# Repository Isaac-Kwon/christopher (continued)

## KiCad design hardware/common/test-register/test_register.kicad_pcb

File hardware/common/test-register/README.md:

# 테스트 레지스터 보드 (Phase 3.0, 산출물 4)

작성일: 2026-11-15 · 상태: **회로도(KiCad 10) + 스위치 수준 시뮬레이션 통과 + 부품 배치(미배선) PCB, 결정 0003 8.1절(R1–R8) 반영(3.3절), 배선·실기 시험은 아직** · 관련: `docs/decisions/0001-test-register-timing.md`, `docs/decisions/0003-interfaces.md`, `hardware/common/design-brief.md` 4.2·4.5·12절(결정 10), `hardware/common/unit-tester/README.md` 3.4절(커넥터 규약), `report/figures/hw-register-circuit.tex`

**표기.** **(추정)** 은 계산·경험에 따른 값으로 실측 전이고, **(미확인)** 은 부품 번호·사양을 데이터시트로 확인하지 못한 것이다. 시뮬레이션이 쓴 릴레이 시간은 결정 0001의 표 값이다.

## 1. 한 줄 요약

감지 릴레이 K1–K26이 `STROBE` 창 안에서 자기 유지로 잡히고(선마다 역류 차단 다이오드), 통과 릴레이 P·정지 릴레이 S·판정 접점 j가 `STROBE`가 끝난 뒤 `JUDGE` 구간에 "26선이 전부 통전되지는 않았는가"를 판정하며, `CLEAR` 구간에 유지 버스 H를 끊어 K와 P를 놓는다. 정지하면 S가 자기 유지하고 H를 우회시켜 K 26개의 상태(램프 표시)를 붙들며, `RUN`을 내리고 시험 전압을 끊는다. 신호 릴레이(G6S-2, DPDT) 34개, 표시 구동 MOSFET 28개.

## 2. 파일

| 파일 | 내용 |
|---|---|
| `gen_register.py` | KiCad 10 회로도 생성(표준 라이브러리 기호 복사). `test_register.kicad_pro/.kicad_sch`(루트: 제어부·커넥터·전원) + `sense_lanes.kicad_sch`(K 26 레인) |
| `verify_register.py` | 넷리스트 내보내기(kicad-cli) → 스위치 수준·사건 구동 시뮬레이션 + 변형 넷리스트 음성 시험 |
| `gen_pcb.py` | 넷리스트 + 푸트프린트 라이브러리 → `test_register.kicad_pcb`(배치·외곽·넷, 미배선). `--check`: 배치된 기판의 패드 넷 = 회로도, DRC, 래츠넷, 재생성 동일, 음성 시험 |
| `test_register.kicad_*` | 생성물(손으로 고치지 않는다) |

재생성: `python gen_register.py && python gen_pcb.py`, 검증: `python verify_register.py [--quick]`, `python gen_pcb.py --check`. KiCad가 기본 위치에 없으면 환경 변수 `KICAD_SHARE`(기호·푸트프린트), `KICAD_CLI`를 준다.

## 3. 회로 (결정 0001 (c) 채택안과의 대응)

릴레이 접점은 소문자(k, p, s, j, r), 코일은 대문자. 모든 릴레이는 G6S-2 24 V (코일 1 = +, 12 = −; 극 1 = COM 4/NC 3/NO 5, 극 2 = COM 9/NC 10/NO 8).

| 요소 | 참조 | 회로 |
|---|---|---|
| 감지 릴레이 K_i | K1–K26 | 코일은 노드 N_i에 연결. N_i ← 차단 다이오드 D_i ← 선 L_i(J1). 극 1 = 유지 접점(H → N_i), 극 2 = 사슬 접점. 코일 역기전력 다이오드 DF_i |
| 유지 버스 H | | HSUP → `r`(CLEAR 릴레이 K29의 b접점, 두 극 병렬) → H. 정지 중에는 S1의 극 1이 HSUP → H를 우회 |
| 사슬 | | H → k_A → k_B → … → k_Z → PN(P 코일). **26선이 전부 유지 중일 때만 PN이 선다** |
| 통과 릴레이 P | K30 | 코일 PN. 극 1 = 자기 유지(H → p → 다이오드 D33 → PN), 극 2 b접점 = 판정 경로 j → p → S 코일 |
| 판정 접점 j | K28 | `JUDGE` 입력으로 구동되는 릴레이의 a접점(두 극 병렬): +24 V → JNODE |
| 정지 릴레이 S | K31–K33 | 코일 3개를 SN에 병렬(극 6개 필요). S1: H 우회, 자기 유지(HSUP → s → SN). S2: P 구동(HSUP → s → PN, 재출발 잠금), 시험 전압 차단(b접점). S3: `RUN` 차단(b접점), `STOP_LATCH`를 뱅크로 |
| `STROBE` 릴레이 | K27 | `STROBE` 입력(J2 1번 → 직렬 다이오드 D34 → 코일)으로 구동. a접점(두 극 병렬)이 +24 V → S2 b접점 → TEST(J5)를 연결 |
| `CLEAR` 릴레이 r | K29 | `CLEAR` 입력(J2 35번 → D36 → 코일)으로 구동. b접점이 CLEAR 구간에 H의 공급을 끊는다. `JUDGE`(K28)는 J2 34번 → D35 → 코일 |
| 해제 릴레이 | K34 | 앞면 해제 누름 버튼(상시 열림)이 구동. b접점 두 개: `RUN` 경로, HSUP(H와 S 자기 유지의 공급). 누르는 동안 S가 풀리고 K·P가 모두 놓이며 `RUN`이 내려간다 |
| 램프 구동 | Q1–Q26, Q27, Q28 | N_i → 분압(RA 33 k/RB 22 k, Vgs < 12 V) → AO3400A. 드레인 = LAMP_i(J3), 소스 = LAMPGND. Q27이 SN으로 LAMPGND를 0 V에 잇는다(정지 중에만). Q28은 정지 램프(LAMP_STOP) |
| 보드 위 표시 | DL1–DL26, DL27 | N_i → 3.3 k → LED → LAMPGND(정지 중에만 켜짐). DL27 = 정지(S 동작). DI1–DI4 = `STROBE`/`JUDGE`/`CLEAR`/`STOPPED` 입력 표시 |

### 3.1 시간표와 회로의 동작 (60 rpm, 한 위치 38.5 ms)

시뮬레이션은 뱅크가 각 신호를 릴레이 동작 시간만큼 앞서 보내 **접점**의 창이 결정 0001의 표와 같도록 한다(보정, G.1 측정 5).

| 구간 (ms) | 접점 | 일어나는 일 |
|---|---|---|
| 0 – 6 | TEST (K27) | 통전된 선의 D_i → N_i → K_i 코일. K_i 동작(최악 5 ms)하면 k(유지)가 N_i를 H에 이어 스스로 유지 |
| 6 – 12 | | 사슬이 닫혔으면(26선 전부) PN이 서고 P 동작(최악 5 ms, 최대 10 ms까지). p(유지)가 H로 P를 유지, p b접점이 열림 |
| 12 – 19 | j (K28) | P가 놓여 있으면 JNODE → p b접점 → SN 에 전압이 걸려 S 코일 3개 동작(최악 5 ms). S가 동작하면 자기 유지, H 우회, P 잠금, TEST 차단, `RUN` 차단, 램프 점등 |
| 21 – 33 | r (K29) | H 공급이 끊겨 K와 P가 놓임(최악 10 ms → 31 ms). 정지 중이면 S1이 H를 우회하므로 아무것도 놓이지 않는다 |
| 33 – 38.5 | | r이 다시 닫혀 H 복구, 다음 `STROBE` 대기 |

재출발: 해제 버튼(J6 핀 3)을 누르면 K34가 동작해 HSUP이 끊긴다. S의 자기 유지와 H가 함께 끊겨 S, K, P가 모두 놓이고 램프가 꺼지며 `RUN`은 K34가 놓일 때까지 낮다. **버튼은 약 50 ms 이상 누른다(K·P의 복귀 최악 10 ms + K34의 동작 시간)**. K34의 자체 복귀 시간이 접점 튐을 흡수한다.

### 3.2 결정 0001 회로도에서 고친 곳 (보고서 그림 `fig:hw-register`와 달라진 점)

시뮬레이션이 드러낸 것이다. 보고서 그림(`report/figures/hw-register-circuit.tex`)과 결정 0001 본문(3절, 6·7절)에 반영했다(2026-11-16).

1. **사슬의 공급은 +24 V가 아니라 H다.** 사슬을 +24 V에서 먹이면 K가 모두 붙은 위치에서 P의 코일이 CLEAR 중에도 사슬에서 전압을 받아, P의 복귀가 첫 K의 복귀 뒤에야 시작된다(K 3–10 ms + P 3–10 ms). 시뮬레이션에서 H가 복구되는 33 ms 시점에 P가 아직 동작 중이어서 P가 다음 주기까지 남았다(오래 남은 P는 거짓 통과, 곧 놓친 정지). H에서 먹이면 K와 P가 같은 순간(`r`이 열릴 때) 복귀를 시작하므로 결정 0001의 "최악 10 ms" 계산이 성립한다.
2. **P의 자기 유지 접점에 다이오드(D33).** 정지 잠금(S2의 p 구동)이나 사슬이 PN에 전압을 주면 p 접점을 거꾸로 H로 흘러, H가 끊겨야 할 때 끊기지 않는다.
3. **정지 잠금과 S의 자기 유지는 +24 V가 아니라 HSUP에서 받는다.** 그래야 해제 버튼 하나로 S, P, K가 함께 풀린다.
4. **해제 릴레이 K34(추가).** 결정 0001 4절 3항은 해제 버튼으로 S만 풀어도 P가 "다음 복귀 구간에서" K와 함께 풀린다고 했다. 그러나 정지 직후 뱅크가 `CLEAR` 없이 다음 `STROBE`로 넘어가면(정지 중 이미 `CLEAR`가 지나갔다), 정지 위치의 K 26개가 남은 채 다음 위치의 선이 덧붙고 P가 잠겨 있어 **다음 위치에서 정지를 놓친다.** 해제 때 보드가 직접 H를 끊어 K·P를 지우면 뱅크가 재출발 때 `CLEAR`를 한 번 더 내야 하는 요구가 사라진다. (뱅크가 재출발 때 `CLEAR` 한 번을 보장한다면 K34는 빼고 버튼을 S 자기 유지 경로의 b접점으로 쓸 수 있다.)
5. **감지 릴레이의 접점 수.** K 하나에 유지·사슬 두 극이면 충분하다(DPDT 1개). 램프는 접점이 아니라 N_i 전압을 읽는 MOSFET이 구동한다(표시 릴레이 26개의 전류가 H·유지 접점을 지나지 않게 하려는 것).

### 3.3 결정 0003 반영 (8.1절)

| # | 변경 | 상태 |
|---|---|---|
| R1 | 타이밍 입력 셋(J2 1·34·35번)에 직렬 다이오드(핀 → D34·D35·D36 → 코일). 다이오드 + 제너 30 V 클램프(D27–D29, DZ27–DZ29)는 코일 쪽 마디(`STROBE_C` 등)에 그대로, 표시 LED·저항(RI1–RI3)은 핀 쪽에 남겨 풀다운 역할. 시뮬레이션의 지연 가정은 그대로. 이유: 신호가 꺼질 때 코일의 + 쪽이 핀을 약 −31 V까지 끌어내리던 것을 막아 기어식의 광센서 출력과 고측 구동기가 견디게 한다(0003 2.2절) | 적용 |
| R2 | J2 36번 `STOP_LATCH`: "제안" 표기를 지우고 확정 | 적용(4절) |
| R3 | J2 22–23번(`ESTOP_A/B`)과 24–25번(`ILOCK_A/B`): 미연결 → **납땜 점퍼(기본 닫힘) SJ1·SJ2**로 각각 잇는다. 22·23번은 J6의 6·7번으로도 낸다(비상 정지 버튼의 b접점을 달면 SJ1을 끊는다) | 적용 |
| R4 | J6을 4극 → 8극: 5번 = Home 버튼 되돌림 → J2 4번(`HOME`, 풀다운 RR4 100 kΩ), 6·7번 = 비상 정지 버튼, 8번 예약. 레지스터는 `HOME`을 쓰지 않고 뱅크로 곧바로 보낸다 | 적용 |
| R5 | D-sub 세 개의 껍데기(풋프린트 패드 `SH`; 심볼에 핀이 없어 PCB 생성기가 붙임)와 도금 장착 구멍 H1–H4를 `CHASSIS`로, `CHASSIS`–0 V에 RCH1 1 MΩ ∥ CCH1 10 nF/100 V | 적용 |
| R6 | 전원 입력에 직렬 P채널 MOSFET QP1(SOT-223, 드레인 = J4 쪽, 게이트에 DZP1 12 V 제너 + RGP1 100 kΩ), F1·F2 앞 공용, TVS DV1은 그 뒤 | 적용 |
| R7 | 이 README: `STROBE`·`JUDGE`·`CLEAR`는 24 V 레벨로 확정(7절 2번), 뱅크의 요구는 0003 3.3절의 L1–L9, 시작 스위치는 유지형, 표시 코일은 60 mA 이하·다이오드만(7.5절), J2 26–27번은 미연결 유지 | 적용(7절, 4절) |
| R8 | 바뀌지 않는 것: J1의 27–29번 = 0 V, 암수(핀), J3·J4·J5의 핀 배치 | 확인 |

## 4. 커넥터와 핀 배치

D-sub 37은 시프터 보드(J1–J4)와 같은 `DC37_Pins`(보드 쪽 핀, 케이블 쪽 소켓)이며 핀 1–26 = 선 A–Z 규약은 단위 시험기와 같다. 뱅크 제어 커넥터는 시험기 J_C와 겹치는 핀이 같은 번호다.

**J1 — 테스트 레지스터 케이블 (메뉴 패널에서 26선)**

| 핀 | 신호 |
|---|---|
| 1–26 | L_A … L_Z (감지 릴레이 입력) |
| 27–29 | 0 V |
| 30–37 | 예약(미연결) |

**J2 — 뱅크 제어 (시험기 J_C 규약)**

| 핀 | 신호 | 방향 |
|---|---|---|
| 1 | `STROBE` (24 V 레벨, 높음 = 시험 구간) | 뱅크 → 보드 |
| 2 | `RUN` (24 V = 진행 허가, 정지하면 낮음) | 보드 → 뱅크 |
| 3 | `STOPPED` (표시 LED만) | 뱅크 → 보드 |
| 4 | `HOME` (24 V, 앞면 패널의 Home 버튼 되돌림 = J6 5번에서 곧바로. 풀다운 100 kΩ. 레지스터는 쓰지 않는다) | 보드 → 뱅크 |
| 22, 23 | `ESTOP_A`, `ESTOP_B`: 뱅크가 22번으로 내보내고 23번으로 받는다. 보드에서 SJ1(기본 닫힘)이 잇고 J6 6·7번으로도 나간다 | 고리 |
| 24, 25 | `ILOCK_A`, `ILOCK_B`: 같음, SJ2(기본 닫힘) | 고리 |
| 34 | `JUDGE` (24 V, 높음 = 판정 구간) | 뱅크 → 보드 |
| 35 | `CLEAR` (24 V, 높음 = 복귀 구간) | 뱅크 → 보드 |
| 36 | `STOP_LATCH` (**확정**: S 동작 = 24 V, 결정 0003 5.2절) | 보드 → 뱅크 |
| 28–33 | 0 V | |
| 5–21, 26–27, 37 | 미연결 (AT_HOME, END, POS, 뱅크 전원 26–27: 이 보드는 쓰지 않는다. 예약 핀은 어느 보드에서도 잇지 않는다) | |

타이밍 입력(1·34·35번)은 24 V 레벨이고 핀 쪽에 음전압을 내보내지 않는다(R1). 받는 쪽 규격: 18 V 이상에서 켜지고 2.4 V 이하에서 꺼진다, 핀당 15 mA 이하(코일 약 8 mA, 직렬 다이오드 0.7 V를 빼면 코일에 약 22.3 V = 정격의 93 %).

**J3 — 표시(램프 패널)**

| 핀 | 신호 |
|---|---|
| 1–26 | LAMP_A … LAMP_Z. 열린 드레인: **낮음 = 그 글자의 표시 릴레이(또는 램프)를 켠다**. 정지 중 K_i가 유지 중인(= 시험 순간에 통전된) 글자만 켜진다 |
| 27 | LAMP_STOP (낮음 = 정지 램프) |
| 28–30 | +24 V (F2 2 A 보호, 표시 릴레이 코일의 + 쪽) |
| 31–37 | 0 V |

표시 쪽: 클리어 케이스 범용 종속 릴레이(결정 10)의 코일을 +24 V와 LAMP_i 사이에 연결하고, 코일마다 역기전력 다이오드를 **표시 쪽**에 둔다. 켜진 램프를 "통전된 글자"로 볼지 "꺼진 글자(스테커 후보)"로 볼지는 표시 릴레이의 a접점/b접점 선택으로 정한다(design-brief 4.5·4.6절의 표현이 엇갈린다는 결정 0001 4절 지적에 대한 처리: 보드는 한 극성만 내고 표시 쪽이 고른다).

**J4** 24 V 입력 (1 = +24 V, 2 = 0 V, 스크루 단자; 역극성 P채널 MOSFET QP1 → F1·F2) · **J5** 시험 전압 선 (1 = TEST: `STROBE` 중 +24 V, 2 = 0 V; 메뉴 패널의 시험 선 플러그로) · **J6** 앞면 패널, 8극 (1 = +24 V 스위치 공통, 2 = 시작 스위치 되돌림(**유지형**: 켜짐/꺼짐이 남는 스위치. 순간 버튼과 자기 유지 릴레이를 따로 두지 않는다), 3 = 해제 누름 버튼 되돌림(상시 열림, 50 ms 이상), 4 = 0 V, 5 = Home 버튼 되돌림 → J2 4번, 6·7 = 비상 정지 버튼의 b접점 → J2 22·23번(버튼이 없으면 SJ1 닫힘), 8 예약). D-sub 껍데기·장착 구멍 = `CHASSIS`(0 V가 아님).

## 5. 릴레이 수와 전력

| 용도 | 수 | 부품 |
|---|---:|---|
| 감지 K | 26 | G6S-2 DC24 (DPDT 신호 릴레이, 투명 케이스 범용 아님: 결정 10) |
| 통과 P | 1 | 같음 |
| 정지 S | 3 | 같음, 코일 병렬 (접점 극 6개 필요) |
| `STROBE`·`JUDGE`·`CLEAR` 릴레이 | 3 | 같음 (코일 역기전력은 다이오드 + 제너 30 V 직렬: 복귀 1.5–4 ms) |
| 해제 | 1 | 같음 |
| **신호 릴레이 합계** | **34** | 표시용 종속 릴레이 26 + 정지 램프는 표시 쪽 부품(보드 밖) |

그 밖: 다이오드 1N4148W 62(차단 26, 코일 26, 클램프·유지 7, 타이밍 입력 직렬 3) + 제너 3(30 V) + 제너 1(12 V 게이트) + TVS 1, MOSFET AO3400A 28 + 직렬 P채널 1, 저항 91, LED 31, PTC 2, 전해 커패시터 2(100 µF/35 V) + 10 nF 1, 납땜 점퍼 2, D-sub 37 3, 스크루 단자 3(J6은 8극), 도금 장착 구멍 4. 넷리스트의 부품은 269개.

전류 **(추정)**: 코일 한 개 약 8 mA(24 V, 결정 0001). 최악(26 K 유지 + P + S + 타이밍·해제 릴레이)은 0.3 A 안팎이고 정지 중 보드 위 LED가 0.17 A를 더한다. 논리 쪽 F1은 1.1 A 유지형을 둔다. 표시 쪽 전류는 보드를 지나지 않고 J3의 +24 V → 표시 릴레이 → LAMP_i → Q_i/Q27 → 0 V로 흐른다. 26개가 모두 켜지고 코일이 약 60 mA라면 1.6 A이므로 F2는 2 A 유지형, Q27은 AO3400A(5.7 A)다. 표시 릴레이의 실제 코일 전류는 부품을 정하면 확인한다.

## 6. 검증

### 6.1 ERC와 넷리스트
`kicad-cli sch erc`: 위반 0(오류·경고 0). 넷리스트 269부품·295넷.

### 6.2 스위치 수준 시뮬레이션 (`verify_register.py`)
넷리스트의 핀 소속만으로 릴레이 접점·다이오드·MOSFET·퓨즈를 풀어 HIGH/LOW를 구하고(둘 다면 단락으로 보고), 릴레이는 코일이 동작(복귀) 시간 동안 끊김 없이 구동될 때만 바뀐다. 시간은 사건 구동(ms)이다. 릴레이 시간 **(결정 0001 표)**: K·P·S·해제 동작 2.5–5 ms(접점 안정 포함), 복귀 3–10 ms(다이오드); `STROBE`·`JUDGE`·`CLEAR` 릴레이 동작 2.5–4 ms, 복귀 1.5–4 ms. 시험대는 뱅크(신호)와 메뉴 배선망(통전된 선 집합 A를 `STROBE` 중에만 시험 선에 잇고, 그 밖에는 무관한 집합 B를 시험 선에 잇는다: 드럼이 움직이는 동안의 역류 경로 시험)을 흉내 낸다.

결과(전체 실행, `python verify_register.py`):

- **통과**(결정 0003 반영 후 같은 값): 438 위치 주기, 176회 정지, 26선 전부 통전 때 거짓 정지 0. 확인 항목: K가 통전된 선만 정확히 유지, P는 26선 전부일 때만 동작, S는 26선이 전부는 아닐 때만 동작·유지, 램프(J3 구동선과 보드 LED)는 **정지 중에만** 유지된 패턴을 보이고, `CLEAR`가 정지가 아닐 때 모든 릴레이를 놓으며, 정지 중에는 K·P·S·램프가 뒤이은 주기(뱅크가 `RUN`을 무시하고 계속 돌 때, 다른 패턴으로)에도 얼어 있고 시험 전압이 끊겨 있으며, 해제가 모두 지우고 `RUN`을 되돌린다.
- 사례: 26선 전부(연속 3위치) / 25선(글자별 26가지) / 1선(26가지) / 0선 / 무작위 부분집합 120(크기 0–26) / 정지·정지 중 주행·해제를 섞은 순서 12 / 모든 릴레이가 최악·최선 시간인 모서리 사례.
- **놓친 정지 시험**: 비정상 `STROBE` 창(2–8 ms)과 무작위 릴레이 시간 60회에서 **놓친 정지 0**, 거짓 정지 6(창이 K 동작보다 짧을 때: 안전한 쪽).
- **최악 릴레이 시간에서의 최소 여유(보드가 뱅크에 요구하는 값)**: `STROBE` 전기적 창 ≥ 5.0 ms(K 최악 동작), `JUDGE` 접점 폭 ≥ 5.0 ms(S 최악 동작; 이보다 짧으면 **정지를 놓친다**), `CLEAR` 접점 폭 ≥ 10.0 ms(K 최악 복귀; 이보다 짧으면 H가 복구될 때 K가 다시 붙어 **지워지지 않는다**). 결정 0001의 창 6 / 7 / 12 ms는 이를 만족한다.
- **음성 시험 18가지**(변형 넷리스트는 모두 실패해야 한다): 차단 다이오드 뒤집기(2), K 유지·사슬 접점 NO/NC 바꾸기(3), P의 자기 유지·판정 경로(2), S1의 자기 유지·H 우회, S2의 P 잠금·시험 차단, S3의 `RUN` 차단, `STROBE` 접점, `CLEAR` 릴레이, 해제 릴레이, `JUDGE`/`CLEAR` 입력 바꾸기, 램프 두 선 바꾸기, 시험 선 두 개 바꾸기. 모두 검출됨.

- **드럼 선 무전류 검사 (결정 0003 L9, 2026-11-16).** 정적: J1의 각 선 L_i 마디는 J1.i와 차단 다이오드 D_i 애노드뿐이고(D_i 캐소드 = K_i 코일 +), 시험 전압 선 J5.1은 K27의 NO 접점 두 개뿐이다. 동적: 모든 평가 시점(JUDGE·CLEAR·정지·해제 포함)에서 K27 접점이 열려 있으면 어떤 J1 선도 HIGH가 아니다(선 전류 = 0; K의 자기 유지·H·LED·램프 구동 경로는 D_i 뒤에 있어 선으로 새지 않는다). 결과: 위반 0. 음성 시험: 차단 다이오드 D5 우회(선을 K5 코일 마디에 붙임, 정적 검사와 동적 검사 단독 둘 다 검출), J1.9를 K9 유지 접점 공통에 붙임, 선 두 개 바꾸기. 따라서 `STROBE` 접점이 열린 뒤 드럼 접점이 떨어져도 전류가 없다(기어식 L9 예외, 0003 3.4절).

한계: 접점 튐은 모델에 없다(동작 시간에 안정 시간을 포함). 릴레이 코일 전압 강하(메뉴 배선망의 직렬 저항, 정격 90 % 조건)는 보지 않는다. 판정은 스위치 수준이므로 아날로그 특성(MOSFET 문턱, LED 전류)은 계산으로만 확인했다.

### 6.3 PCB (배치, 미배선)
`test_register.kicad_pcb`: 250 × 150 mm(결정 0003 반영으로 140 → 150), 2층, 푸트프린트 269개를 배치하고 넷을 가져와 연결 가능한 상태(고무줄)다. 커넥터 J1·J2·J3(D-sub 37)는 아래 가장자리에 놓아 케이블이 한 면으로 나온다. K 레인 26개는 3행 × 9열 격자이며 레인마다 릴레이 옆에 차단·코일 다이오드, 게이트 분압 저항 2, 램프 LED·저항, MOSFET이 붙는다. 위쪽 띠에 제어 릴레이 K27–K34와 그 다이오드, 표시·풀다운 소자, 오른쪽 위에 전원·시험·패널 단자와 퓨즈·커패시터·TVS, 장착 구멍 4개(M3).

`python gen_pcb.py --check`(`kicad-cli pcb drc --schematic-parity` 포함): **DRC 위반 0**, 연결 안 됨(배선할 고무줄) 499개 표시(보고서 한도)이고 pcbnew 래츠넷은 590 = Σ(핀 − 1) + 중복 번호 패드 4(D-sub 껍데기 `SH` 3 + MOSFET 탭 1)이다. 모든 패드의 넷이 회로도 넷리스트와 같고(껍데기 `SH` 패드는 `CHASSIS`), 회로도 패리티에서는 `SH` 패드 6개(심볼에 핀이 없음)만 다르다. 기판은 두 번 생성해도 바이트 단위로 같고, 패드 두 개의 넷을 바꾼 복사본·껍데기 패드를 0 V로 옮긴 복사본은 검출된다. 새 부품(QP1·DZP1·RGP1·RR4·RCH1·CCH1·SJ1·SJ2·D34–D36)은 위쪽·오른쪽 띠에 있다.

## 7. 미결 사항

1. **배선.** 이 기계에는 자동 배선기가 없어 배선하지 못했다. 선택지: 자동 배선기(Freerouting 등)를 쓸 수 있는 환경에서 `test_register.kicad_pcb`를 열어 배선, 또는 레인이 같은 모양이므로 레인 하나를 손으로 배선해 복제하는 스크립트 방식. 레인 간 공용 넷(H, GND, LAMPGND, 사슬 CH1–CH25, 선 L_i, 램프 LAMP_i)이 대부분이다. 전류 1 A 안팎 구간(GND, H, +24V, 표시 쪽)은 굵게 한다.
2. (닫힘, 결정 0003 2·3절) **뱅크가 지킬 요구**(0003 3.3절 L1–L9 참고; 아래는 접점 면의 값): `STROBE` 전기적 창 ≥ 5 ms(보정), `JUDGE` 접점 ≥ 5 ms이고 `STROBE` 시작 뒤 10 ms 이후(K 5 + P 5), `CLEAR` 접점 ≥ 10 ms이며 `JUDGE`가 끝난 뒤, 세 신호는 24 V 레벨이며 보드의 릴레이가 동작 시간만큼 늦춘다(뱅크가 앞서 낸다). 입력은 **24 V 레벨로 확정**(무전압 접점 방식은 쓰지 않는다; K27–K29는 그대로 둔다). 커넥터 면(뱅크가 지킬 값, 보정 없이 성립): `STROBE` ≥ 7.5, `JUDGE` ≥ 7.5, `CLEAR` ≥ 12.5 ms, 최단 주기 34.5 ms.
3. 결정 0001 4절의 "램프 극성": 이 보드는 켜진 쪽 = K 유지(통전된 글자)이며 표시 쪽에서 반전한다(4절 J3).
4. (닫힘, 결정 0003 R2·R4) J2 핀 36 `STOP_LATCH`는 확정, J6 패널은 8극, D-sub 암수는 핀(수)이다. `STOPPED`는 표시만 한다.
5. 사슬 접점 26개 직렬의 신뢰도(접점 저항 누적, G6S-2 접점 정격 확인), 코일 전압(메뉴 배선망 직렬 저항 + 다이오드 0.7 V에서 90 % 이상인지, G.2 측정 7), 코일 복귀 시간(다이오드 방식 3–10 ms **(추정)**, 측정 4)은 실측으로 확정한다.
6. (닫힘, 결정 0003 7.4절) 시험 전압 선(J5)은 F1(1.1 A)을 거치며 따로 퓨즈를 두지 않는다. 메뉴 배선망의 어느 선이 프레임이나 0 V 기준선에 닿아도 F1이 끊고 그 위치는 거짓 정지(안전한 쪽)가 된다. 직렬 저항은 감지 릴레이의 코일 전압을 깎으므로 두지 않는다. 전원 입력은 직렬 P채널 MOSFET이 역극성을 막는다.
7. 퓨즈(PTC) 번호, AO3400A의 게이트 한계(분압으로 9.6 V), 표시 릴레이 코일 전류는 **(미확인)** 이다. 부품 번호는 종류를 보여 주는 예다.
8. (닫힘, 2026-11-16) 보고서 그림 `fig:hw-register`와 결정 0001 본문을 3.2절의 변경에 맞춰 고쳤다(사슬 공급 H, P 유지 다이오드, HSUP, 해제 릴레이 K34, 타이밍 입력 다이오드). 두 면의 규칙과 선 무전류는 보고서 그림 `fig:hw-register-faces`, 표 `tab:hw-iface-rules`, 결정 0001 7절.

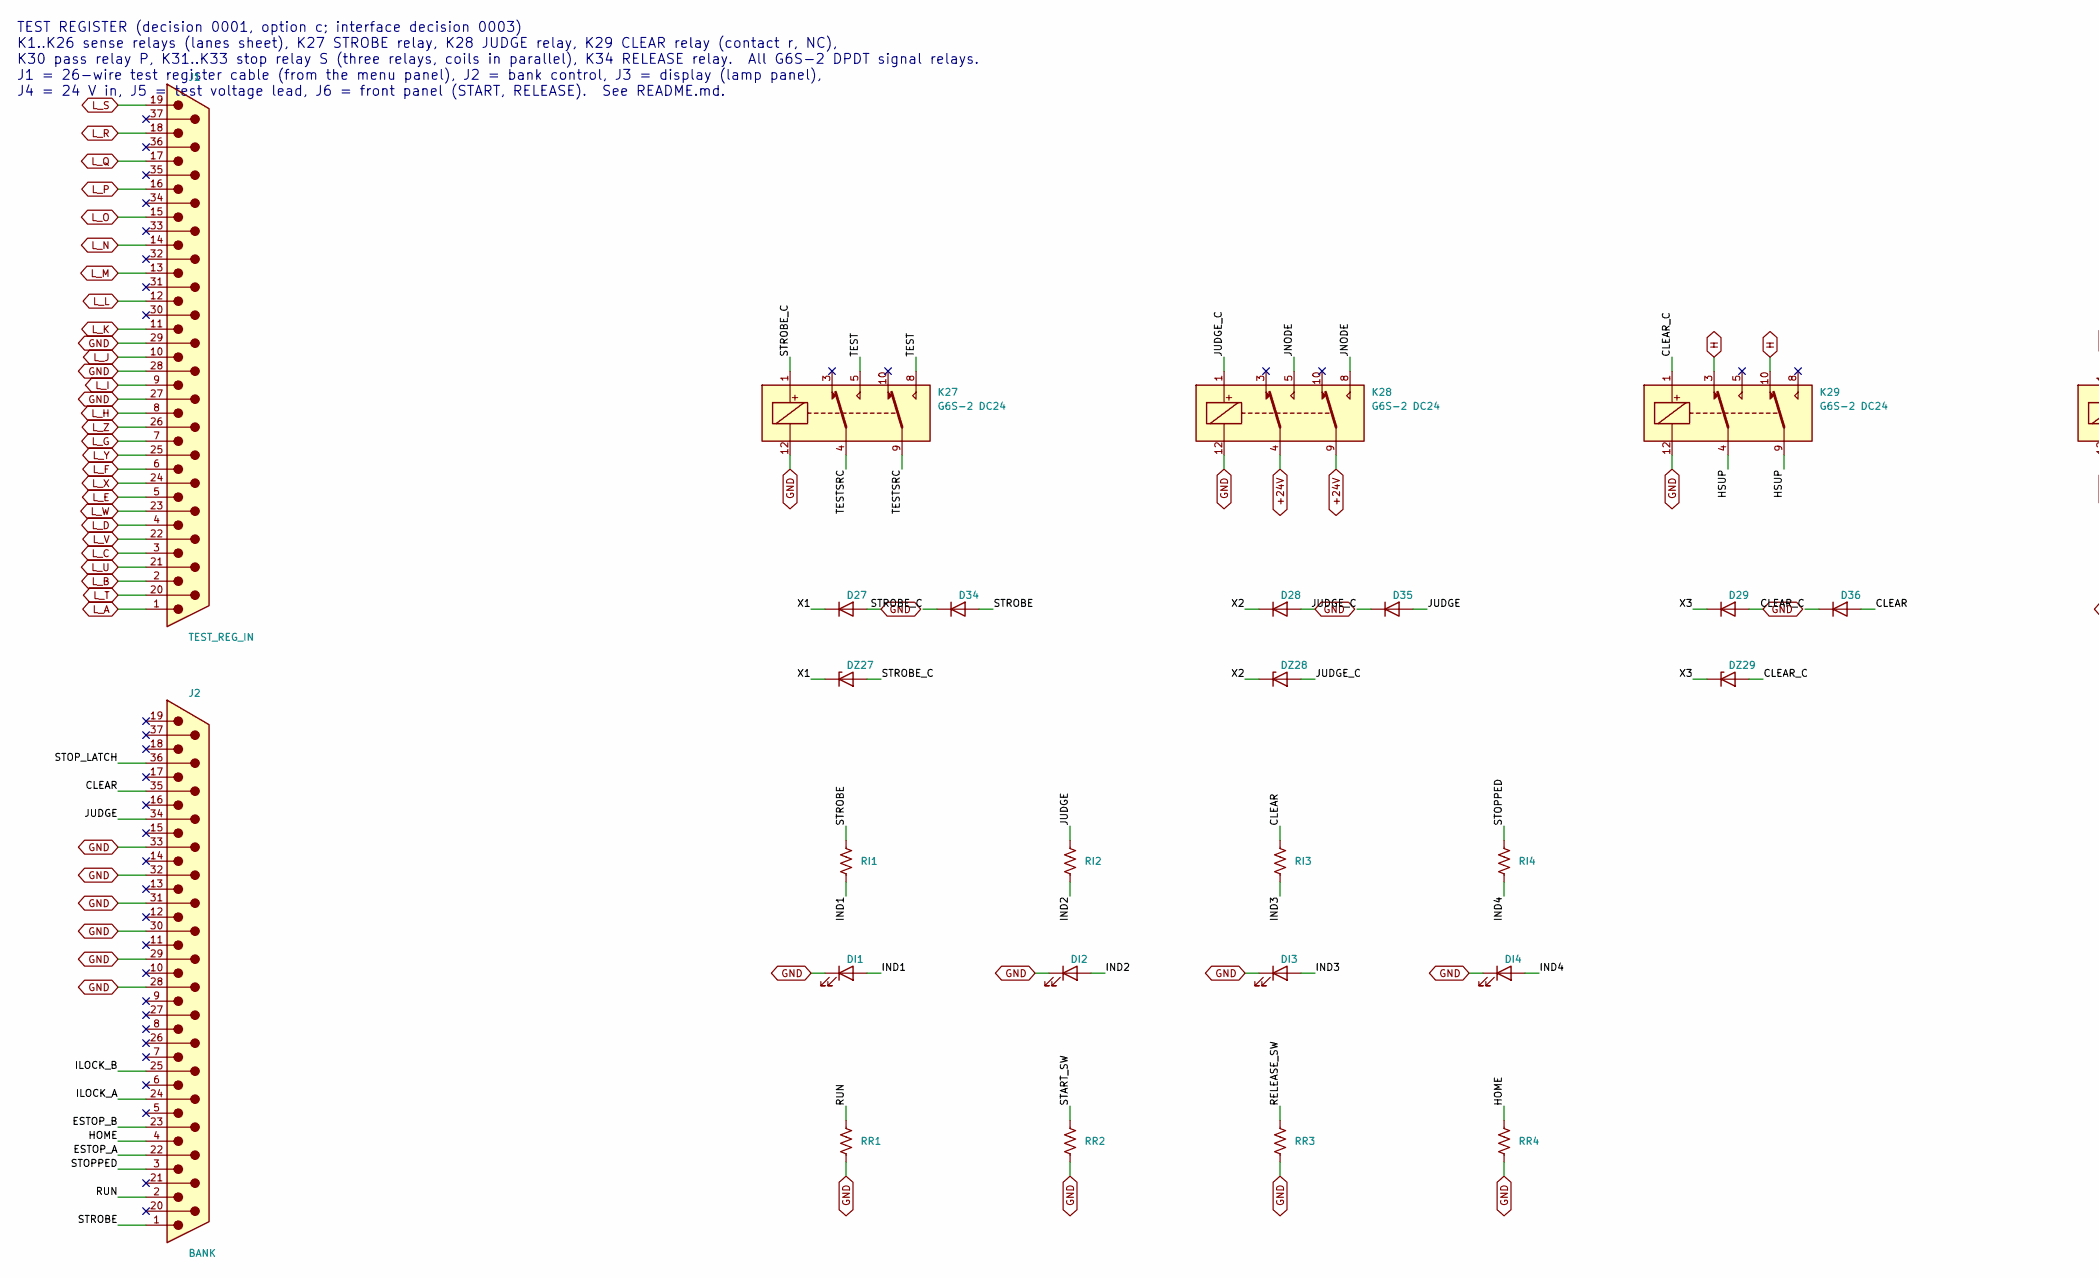
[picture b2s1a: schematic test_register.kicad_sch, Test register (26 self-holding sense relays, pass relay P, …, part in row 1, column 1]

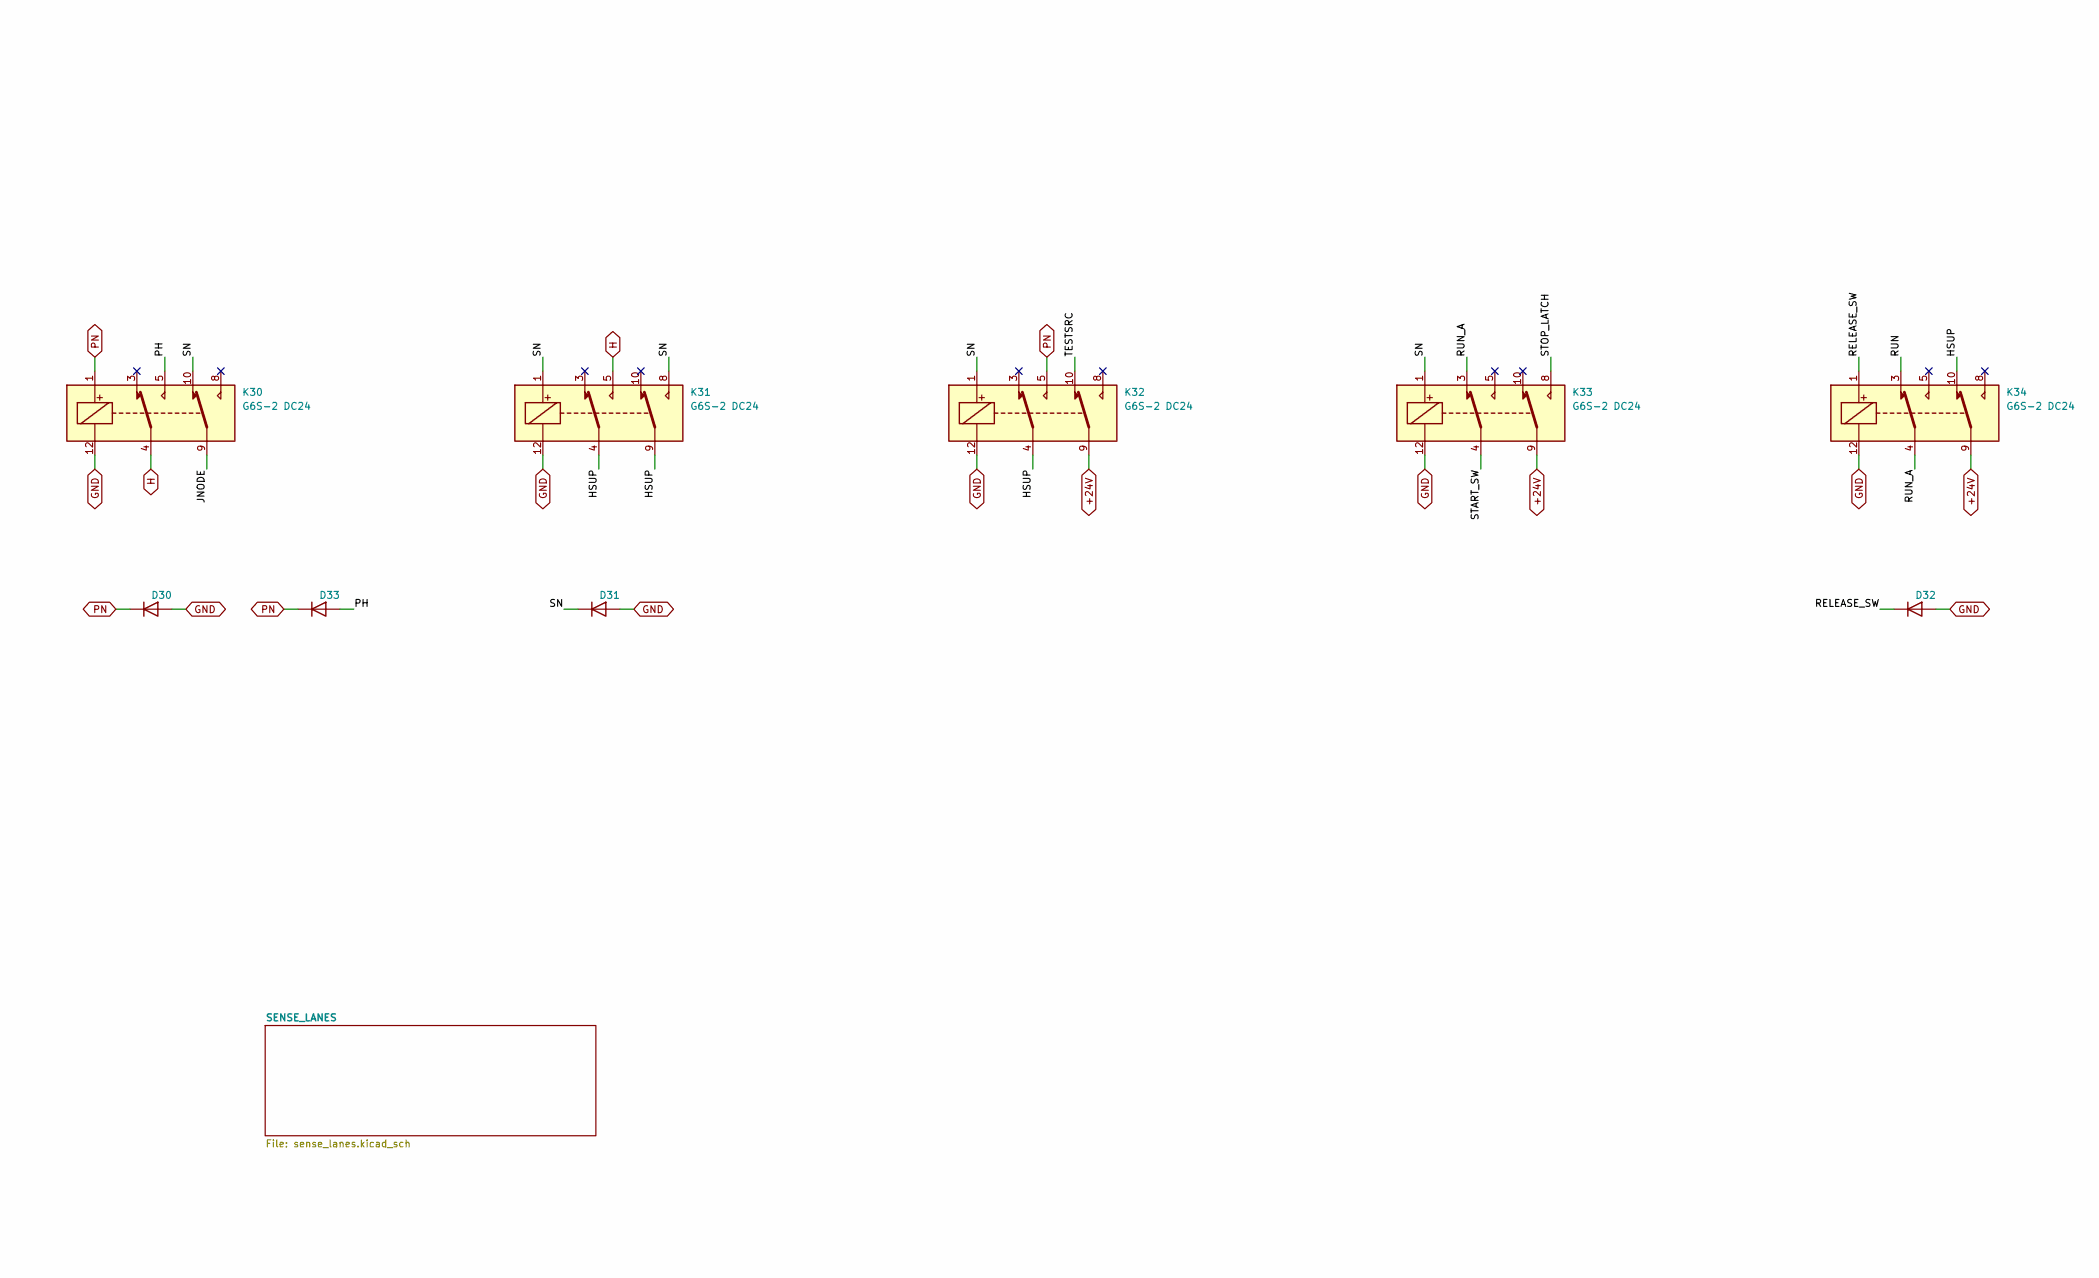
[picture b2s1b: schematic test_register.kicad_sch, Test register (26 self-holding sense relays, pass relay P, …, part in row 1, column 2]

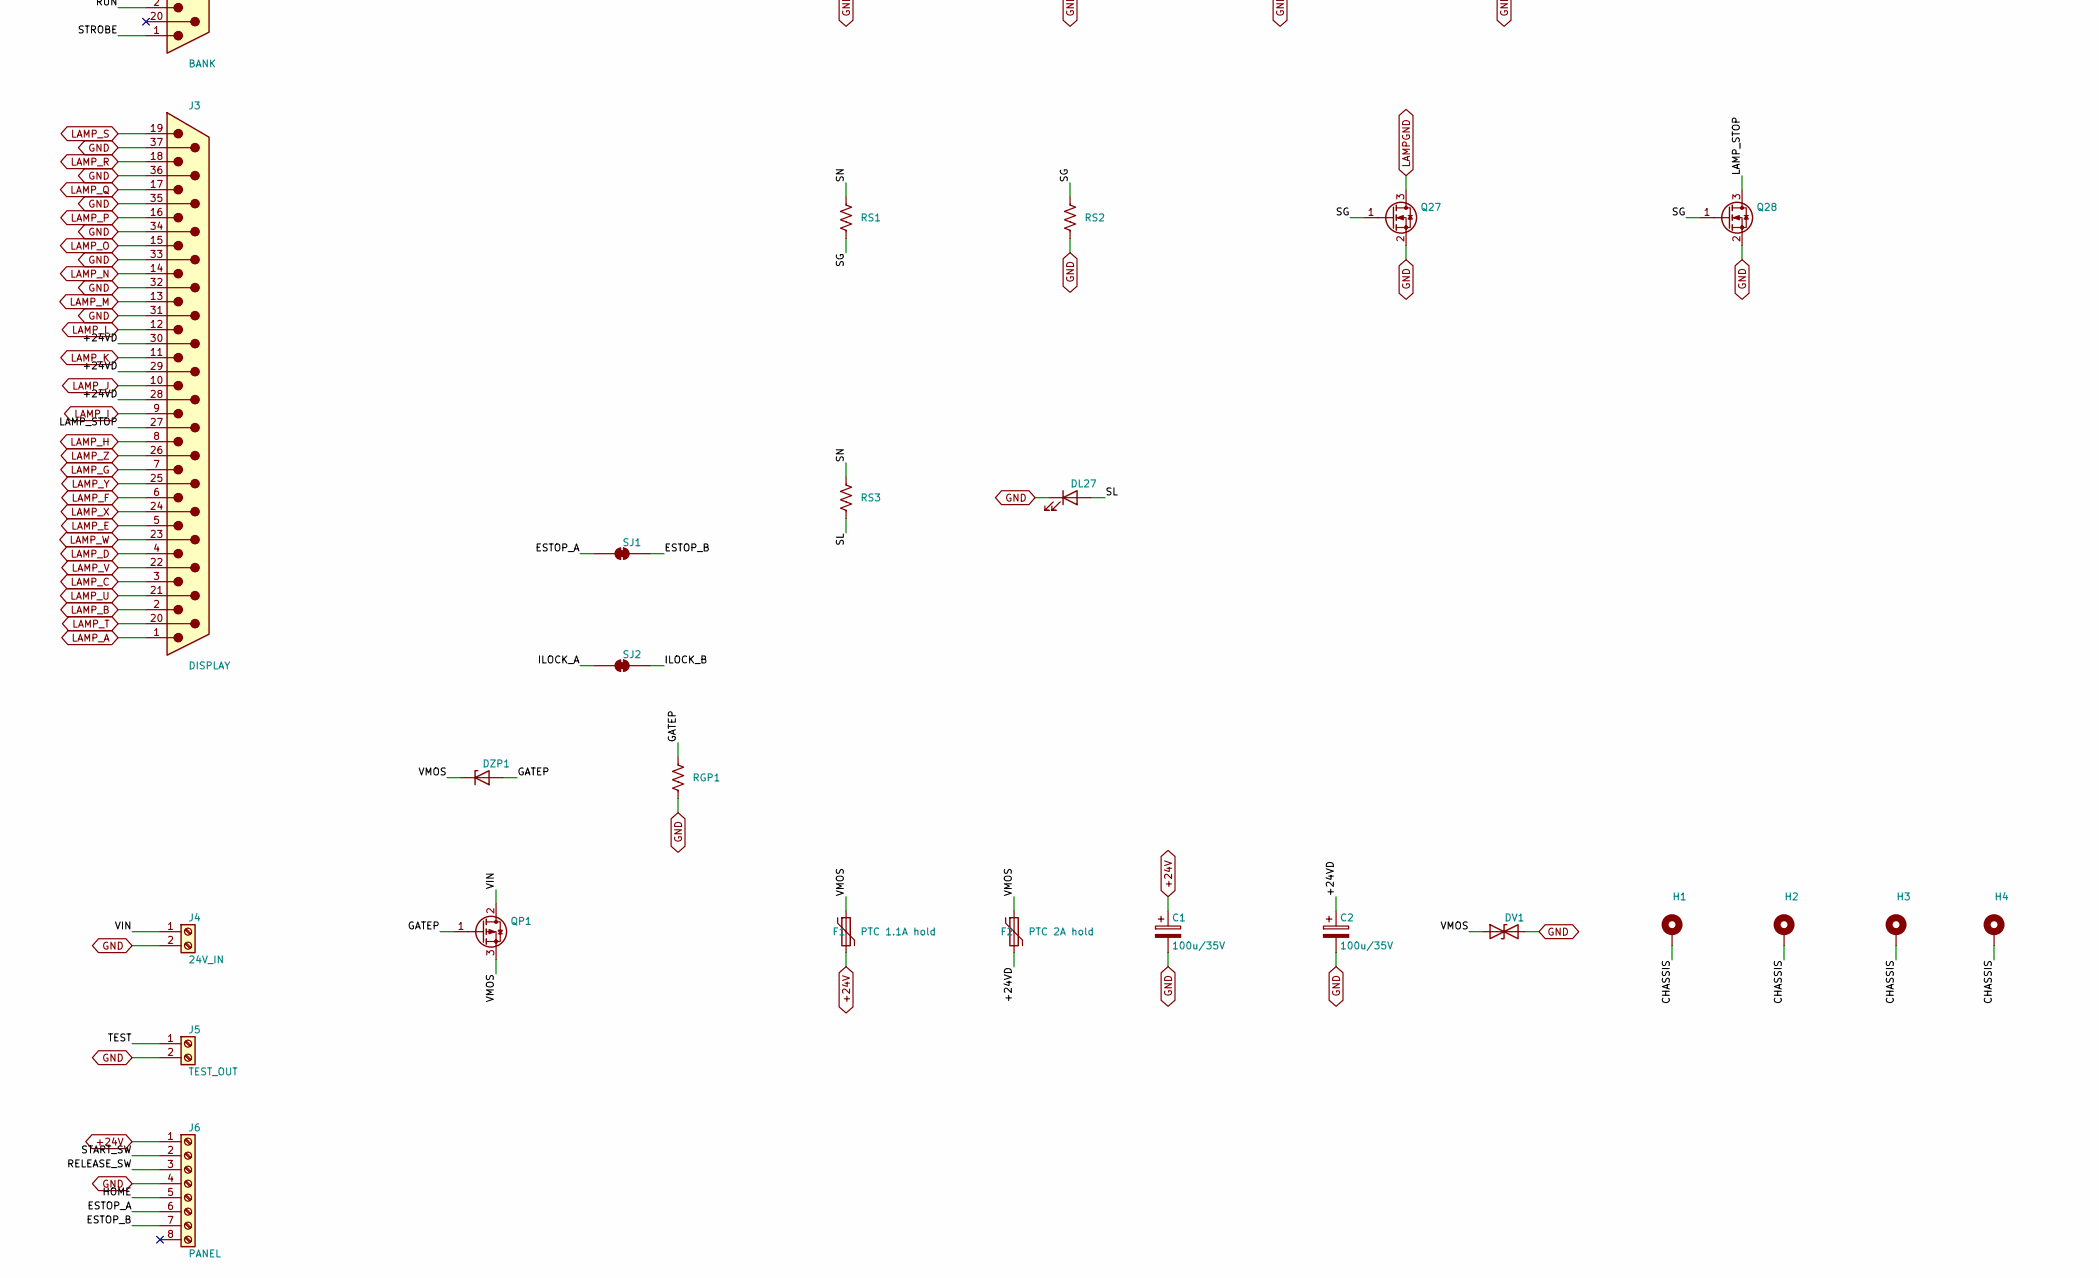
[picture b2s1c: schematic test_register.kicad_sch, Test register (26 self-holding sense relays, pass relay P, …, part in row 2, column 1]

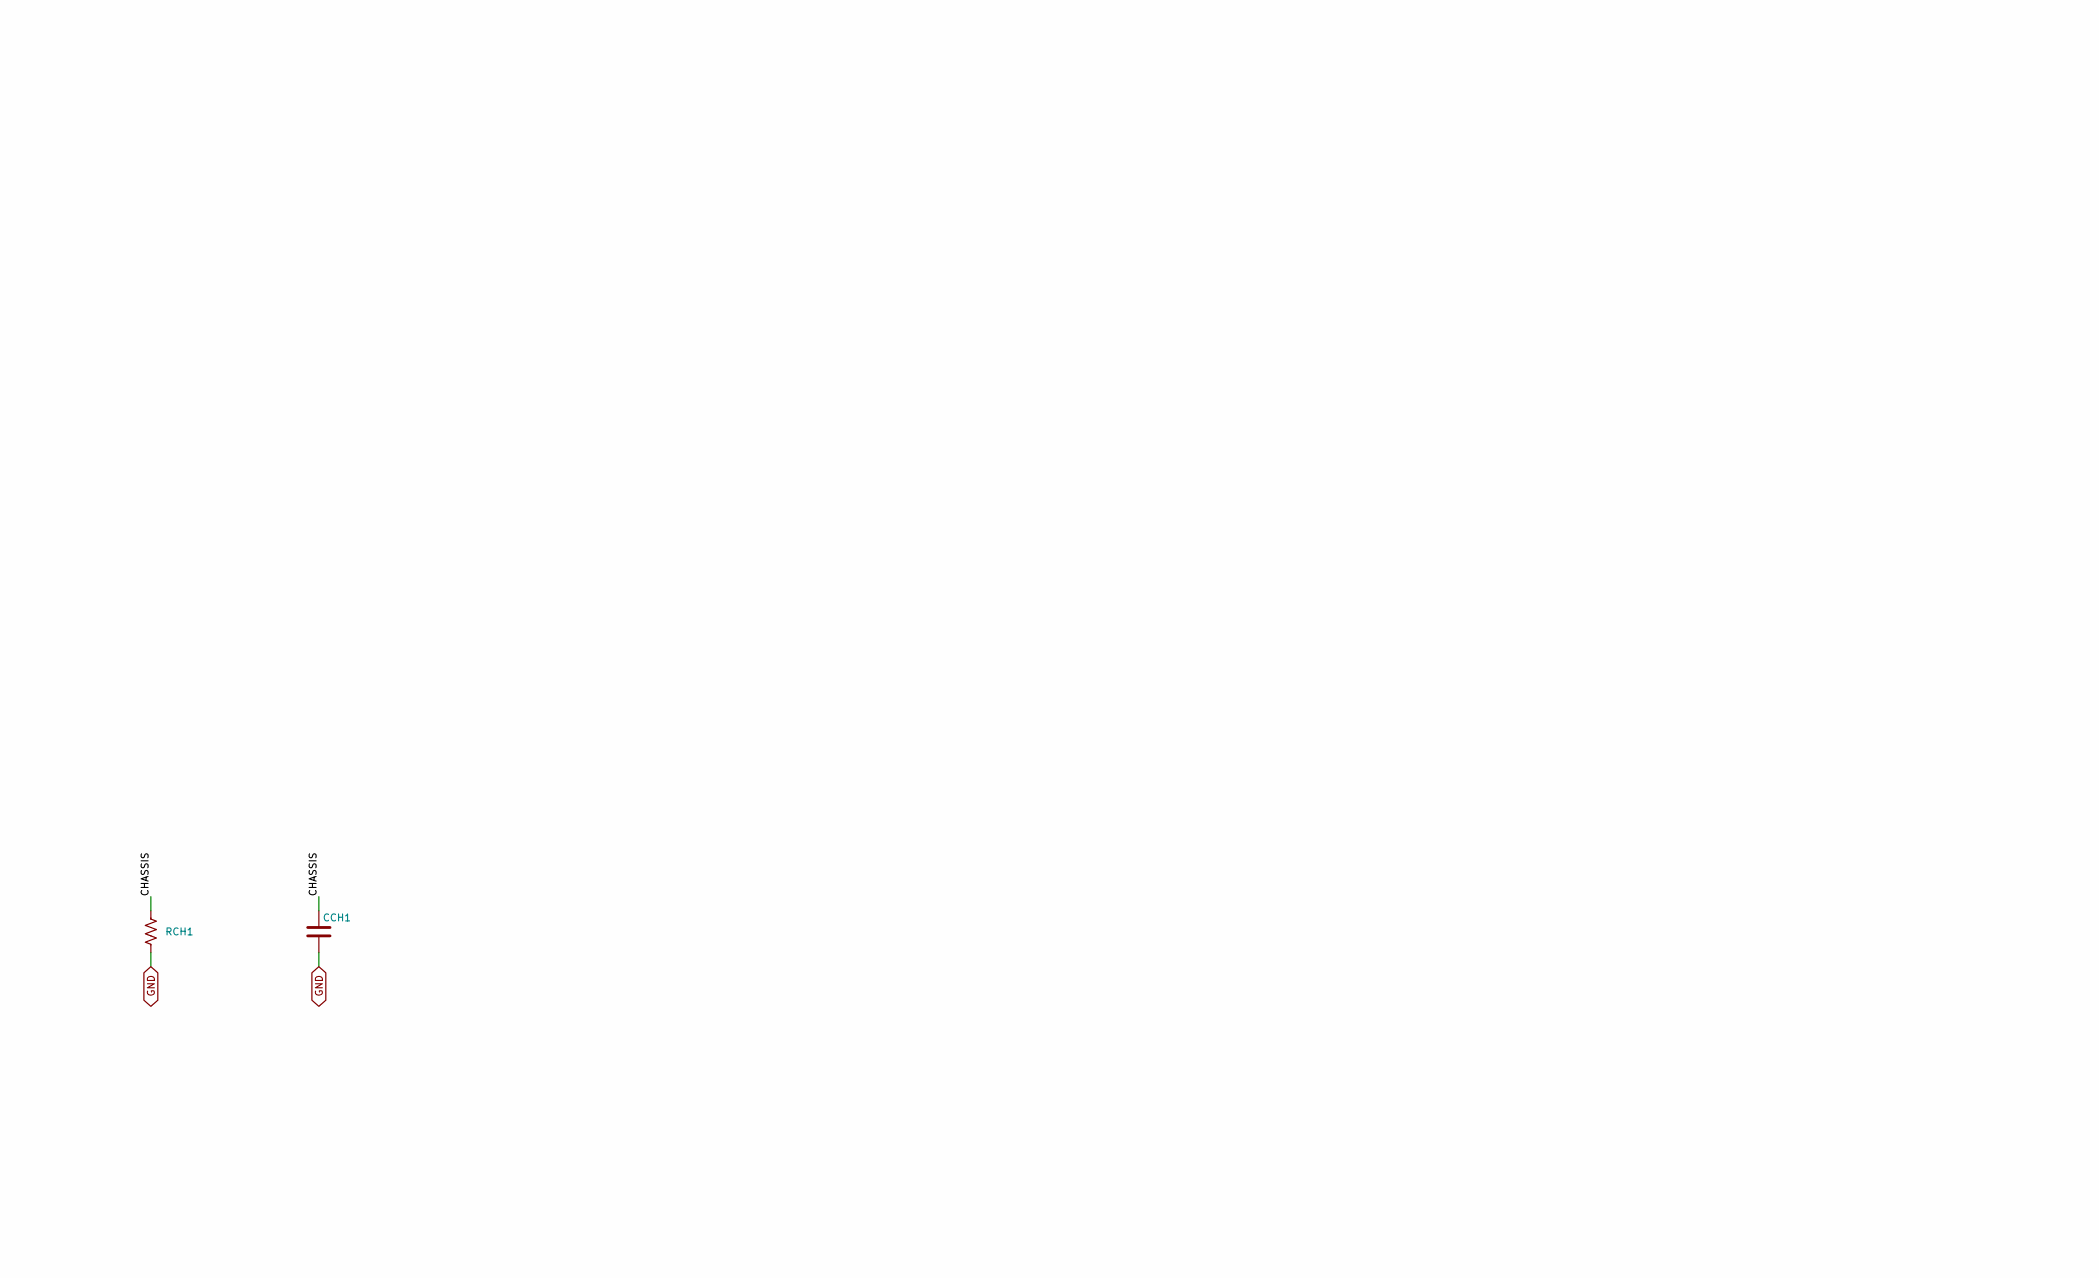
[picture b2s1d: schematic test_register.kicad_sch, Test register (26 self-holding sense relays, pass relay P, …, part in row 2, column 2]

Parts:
C1, C2: 100u/35V; CP_Radial_D8.0mm_P3.50mm
CCH1: 10nF 100V; C_0603_1608Metric
D27, D28, D29, D30, D31, D32, D33, D34, D35, D36: 1N4148W; D_SOD-123
DI1, DI2, DI3, DI4: LED; LED_0603_1608Metric
DL27: LED red; LED_0603_1608Metric
DV1: SMAJ33A; D_SMA
DZ27, DZ28, DZ29: BZT52C30; D_SOD-123
DZP1: 12V; D_SOD-123
F1: PTC 1.1A hold; Fuse_1812_4532Metric
F2: PTC 2A hold; Fuse_2920_7451Metric
H1, H2, H3, H4: MountingHole_Pad; MountingHole_3.2mm_M3_Pad
J1: TEST_REG_IN; DSUB-37_Pins_Horizontal_P2.77x2.84mm_EdgePinOffset9.90mm_Ho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
J2: BANK; DSUB-37_Pins_Horizontal_P2.77x2.84mm_EdgePinOffset9.90mm_Ho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
J3: DISPLAY; DSUB-37_Pins_Horizontal_P2.77x2.84mm_EdgePinOffset9.90mm_Ho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
J4: 24V_IN; TerminalBlock_Phoenix_MKDS-1,5-2-5.08_1x02_P5.08mm_Horizont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
J5: TEST_OUT; TerminalBlock_Phoenix_MKDS-1,5-2-5.08_1x02_P5.08mm_Horizont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
J6: PANEL; TerminalBlock_Phoenix_MKDS-1,5-8-5.08_1x08_P5.08mm_Horizont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
K27, K28, K29, K30, K31, K32, K33, K34: G6S-2 DC24; Relay_DPDT_Omron_G6S-2
Q27, Q28: AO3400A; SOT-23
QP1: P-MOSFET (reverse polarity); SOT-223-3_TabPin2
RCH1: 1M; R_0603_1608Metric
RGP1: 100k; R_0603_1608Metric
RI1, RI2, RI3, RI4: 4.7k; R_0603_1608Metric
RR1: 10k; R_0603_1608Metric
RR2, RR3, RR4: 100k; R_0603_1608Metric
RS1: 33k; R_0603_1608Metric
RS2: 22k; R_0603_1608Metric
RS3: 3.3k; R_0603_1608Metric
SJ1: ESTOP loop (bridged); SolderJumper-2_P1.3mm_Bridged_RoundedPad1.0x1.5mm
SJ2: ILOCK loop (bridged); SolderJumper-2_P1.3mm_Bridged_RoundedPad1.0x1.5mm

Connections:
+24V: C1.1, F1.2, J6.1, K28.4, K28.9, K32.9, K33.9, K34.9
/+24VD: C2.1, F2.2, J3.28, J3.29, J3.30
/CHASSIS: CCH1.1, H1.1, H2.1, H3.1, H4.1, J1.SH, J2.SH, J3.SH, RCH1.1
/CLEAR: D36.2 (A), J2.35, RI3.1
/CLEAR_C: D36.1 (K), DZ29.2 (A), K29.1
/ESTOP_A: J2.22, J6.6, SJ1.1 (A)
/ESTOP_B: J2.23, J6.7, SJ1.2 (B)
/GATEP: DZP1.2 (A), QP1.1 (G), RGP1.1
/HOME: J2.4, J6.5, RR4.1
/HSUP: K29.4, K29.9, K31.4, K31.9, K32.4, K34.10
/ILOCK_A: J2.24, SJ2.1 (A)
/ILOCK_B: J2.25, SJ2.2 (B)
/IND1: DI1.2 (A), RI1.2
/IND2: DI2.2 (A), RI2.2
/IND3: DI3.2 (A), RI3.2
/IND4: DI4.2 (A), RI4.2
/JNODE: K28.5, K28.8, K30.9
/JUDGE: D35.2 (A), J2.34, RI2.1
/JUDGE_C: D35.1 (K), DZ28.2 (A), K28.1
/LAMP_STOP: J3.27, Q28.3 (D)
/PH: D33.2 (A), K30.5
/RELEASE_SW: D32.1 (K), J6.3, K34.1, RR3.1
/RUN: J2.2, K34.3, RR1.1
/RUN_A: K33.3, K34.4
/SG: Q27.1 (G), Q28.1 (G), RS1.2, RS2.1
/SL: DL27.2 (A), RS3.2
/SN: D31.1 (K), K30.10, K31.1, K31.8, K32.1, K33.1, RS1.1, RS3.1
/START_SW: J6.2, K33.4, RR2.1
/STOPPED: J2.3, RI4.1
/STOP_LATCH: J2.36, K33.8
/STROBE: D34.2 (A), J2.1, RI1.1
/STROBE_C: D34.1 (K), DZ27.2 (A), K27.1
/TEST: J5.1, K27.5, K27.8
/TESTSRC: K27.4, K27.9, K32.10
/VIN: J4.1, QP1.2 (D)
/VMOS: DV1.1 (A1), DZP1.1 (K), F1.1, F2.1, QP1.3 (S)
/X1: D27.1 (K), DZ27.1 (K)
/X2: D28.1 (K), DZ28.1 (K)
/X3: D29.1 (K), DZ29.1 (K)
GND: C1.2, C2.2, CCH1.2, D27.2 (A), D28.2 (A), D29.2 (A), D30.2 (A), D31.2 (A), D32.2 (A), DI1.1 (K), DI2.1 (K), DI3.1 (K), DI4.1 (K), DL27.1 (K), DV1.2 (A2), J1.27, J1.28, J1.29, J2.28, J2.29, J2.30, J2.31, J2.32, J2.33, J3.31, J3.32, J3.33, J3.34, J3.35, J3.36, J3.37, J4.2, J5.2, J6.4, K27.12, K28.12, K29.12, K30.12, K31.12, K32.12, K33.12, K34.12, Q27.2 (S), Q28.2 (S), RCH1.2, RGP1.2, RR1.2, RR2.2, RR3.2, RR4.2, RS2.2; also elsewhere on the board
H: K29.3, K29.10, K30.4, K31.5; also elsewhere on the board
LAMPGND: Q27.3 (D); also elsewhere on the board
LAMP_A: J3.1; also elsewhere on the board
LAMP_B: J3.2; also elsewhere on the board
LAMP_C: J3.3; also elsewhere on the board
LAMP_D: J3.4; also elsewhere on the board
LAMP_E: J3.5; also elsewhere on the board
LAMP_F: J3.6; also elsewhere on the board
LAMP_G: J3.7; also elsewhere on the board
LAMP_H: J3.8; also elsewhere on the board
LAMP_I: J3.9; also elsewhere on the board
LAMP_J: J3.10; also elsewhere on the board
LAMP_K: J3.11; also elsewhere on the board
LAMP_L: J3.12; also elsewhere on the board
LAMP_M: J3.13; also elsewhere on the board
LAMP_N: J3.14; also elsewhere on the board
LAMP_O: J3.15; also elsewhere on the board
LAMP_P: J3.16; also elsewhere on the board
LAMP_Q: J3.17; also elsewhere on the board
LAMP_R: J3.18; also elsewhere on the board
LAMP_S: J3.19; also elsewhere on the board
LAMP_T: J3.20; also elsewhere on the board
LAMP_U: J3.21; also elsewhere on the board
LAMP_V: J3.22; also elsewhere on the board
LAMP_W: J3.23; also elsewhere on the board
LAMP_X: J3.24; also elsewhere on the board
LAMP_Y: J3.25; also elsewhere on the board
LAMP_Z: J3.26; also elsewhere on the board
L_A: J1.1; also elsewhere on the board
L_B: J1.2; also elsewhere on the board
L_C: J1.3; also elsewhere on the board
L_D: J1.4; also elsewhere on the board
L_E: J1.5; also elsewhere on the board
L_F: J1.6; also elsewhere on the board
L_G: J1.7; also elsewhere on the board
L_H: J1.8; also elsewhere on the board
L_I: J1.9; also elsewhere on the board
L_J: J1.10; also elsewhere on the board
L_K: J1.11; also elsewhere on the board
L_L: J1.12; also elsewhere on the board
L_M: J1.13; also elsewhere on the board
L_N: J1.14; also elsewhere on the board
L_O: J1.15; also elsewhere on the board
L_P: J1.16; also elsewhere on the board
L_Q: J1.17; also elsewhere on the board
L_R: J1.18; also elsewhere on the board
L_S: J1.19; also elsewhere on the board
L_T: J1.20; also elsewhere on the board
L_U: J1.21; also elsewhere on the board
L_V: J1.22; also elsewhere on the board
L_W: J1.23; also elsewhere on the board
L_X: J1.24; also elsewhere on the board
L_Y: J1.25; also elsewhere on the board
L_Z: J1.26; also elsewhere on the board
PN: D30.1 (K), D33.1 (K), K30.1, K32.5; also elsewhere on the board

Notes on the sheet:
TEST REGISTER (decision 0001, option c; interface decision 0003) K1..K26 sense relays (lanes sheet), K27 STROBE relay, K28 JUDGE relay, K29 CLEAR relay (contact r, NC), K30 pass relay P, K31..K33 stop relay S (three relays, coils in parallel), K34 RELEASE relay. All G6S-2 DPDT signal relays. J1 = 2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
